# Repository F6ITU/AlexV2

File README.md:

# Alexandrie_V2

Dual ADC OpenHPSDR frontend control board

  **Pour plus d'informations, reportez-vous au Wiki de la page [Alexandrie](https://github.com/F6ITU/Alexandrie)**
  **For more information, please refer to the [Alexandrie](https://github.com/F6ITU/Alexandrie) wiki page**

Kicad files

* Control board for Alexiares filter set driven by an Orion/OrionMK2/Anvelina SDR board with dual 16 bits ADC

This board supports the SPI "Alexiares" protocol (also called "J15") of 
the original Hermes SDR board designed by the OpenHPSDR group.

This second version drives a dual RX BPF filter. 
It also remains compatible with older versions of Alex (see assembly notes

As the third generation of Alexiares frontend is not sold by Apache but still under an open hardware licence, 
a new and more "modular" design was needed by many hams wishing to home-build a "Orion class" fontend

A common Gerber set of files will be used for both RX filters (one with a "RX2_GND" relay, one with a strap on the relay footprint)

TX filter depends on user's choice. The original 150W Alexiares lpf (https://github.com/F6ITU/Alexiares_LPF)
or LA2NI Zolotarev 600W LPF (https://github.com/LA2NI/Zolotarev-LPF)
This board could also be used with the new Aries ATU/Zolotarev lpf/Munin400 high power frontend

This work is protected by the TAPR Open Hardware Licence https://www.tapr.org/ohl.html
Original work by Graham Haddock, KE9H and Phil Harman, VK6APH.

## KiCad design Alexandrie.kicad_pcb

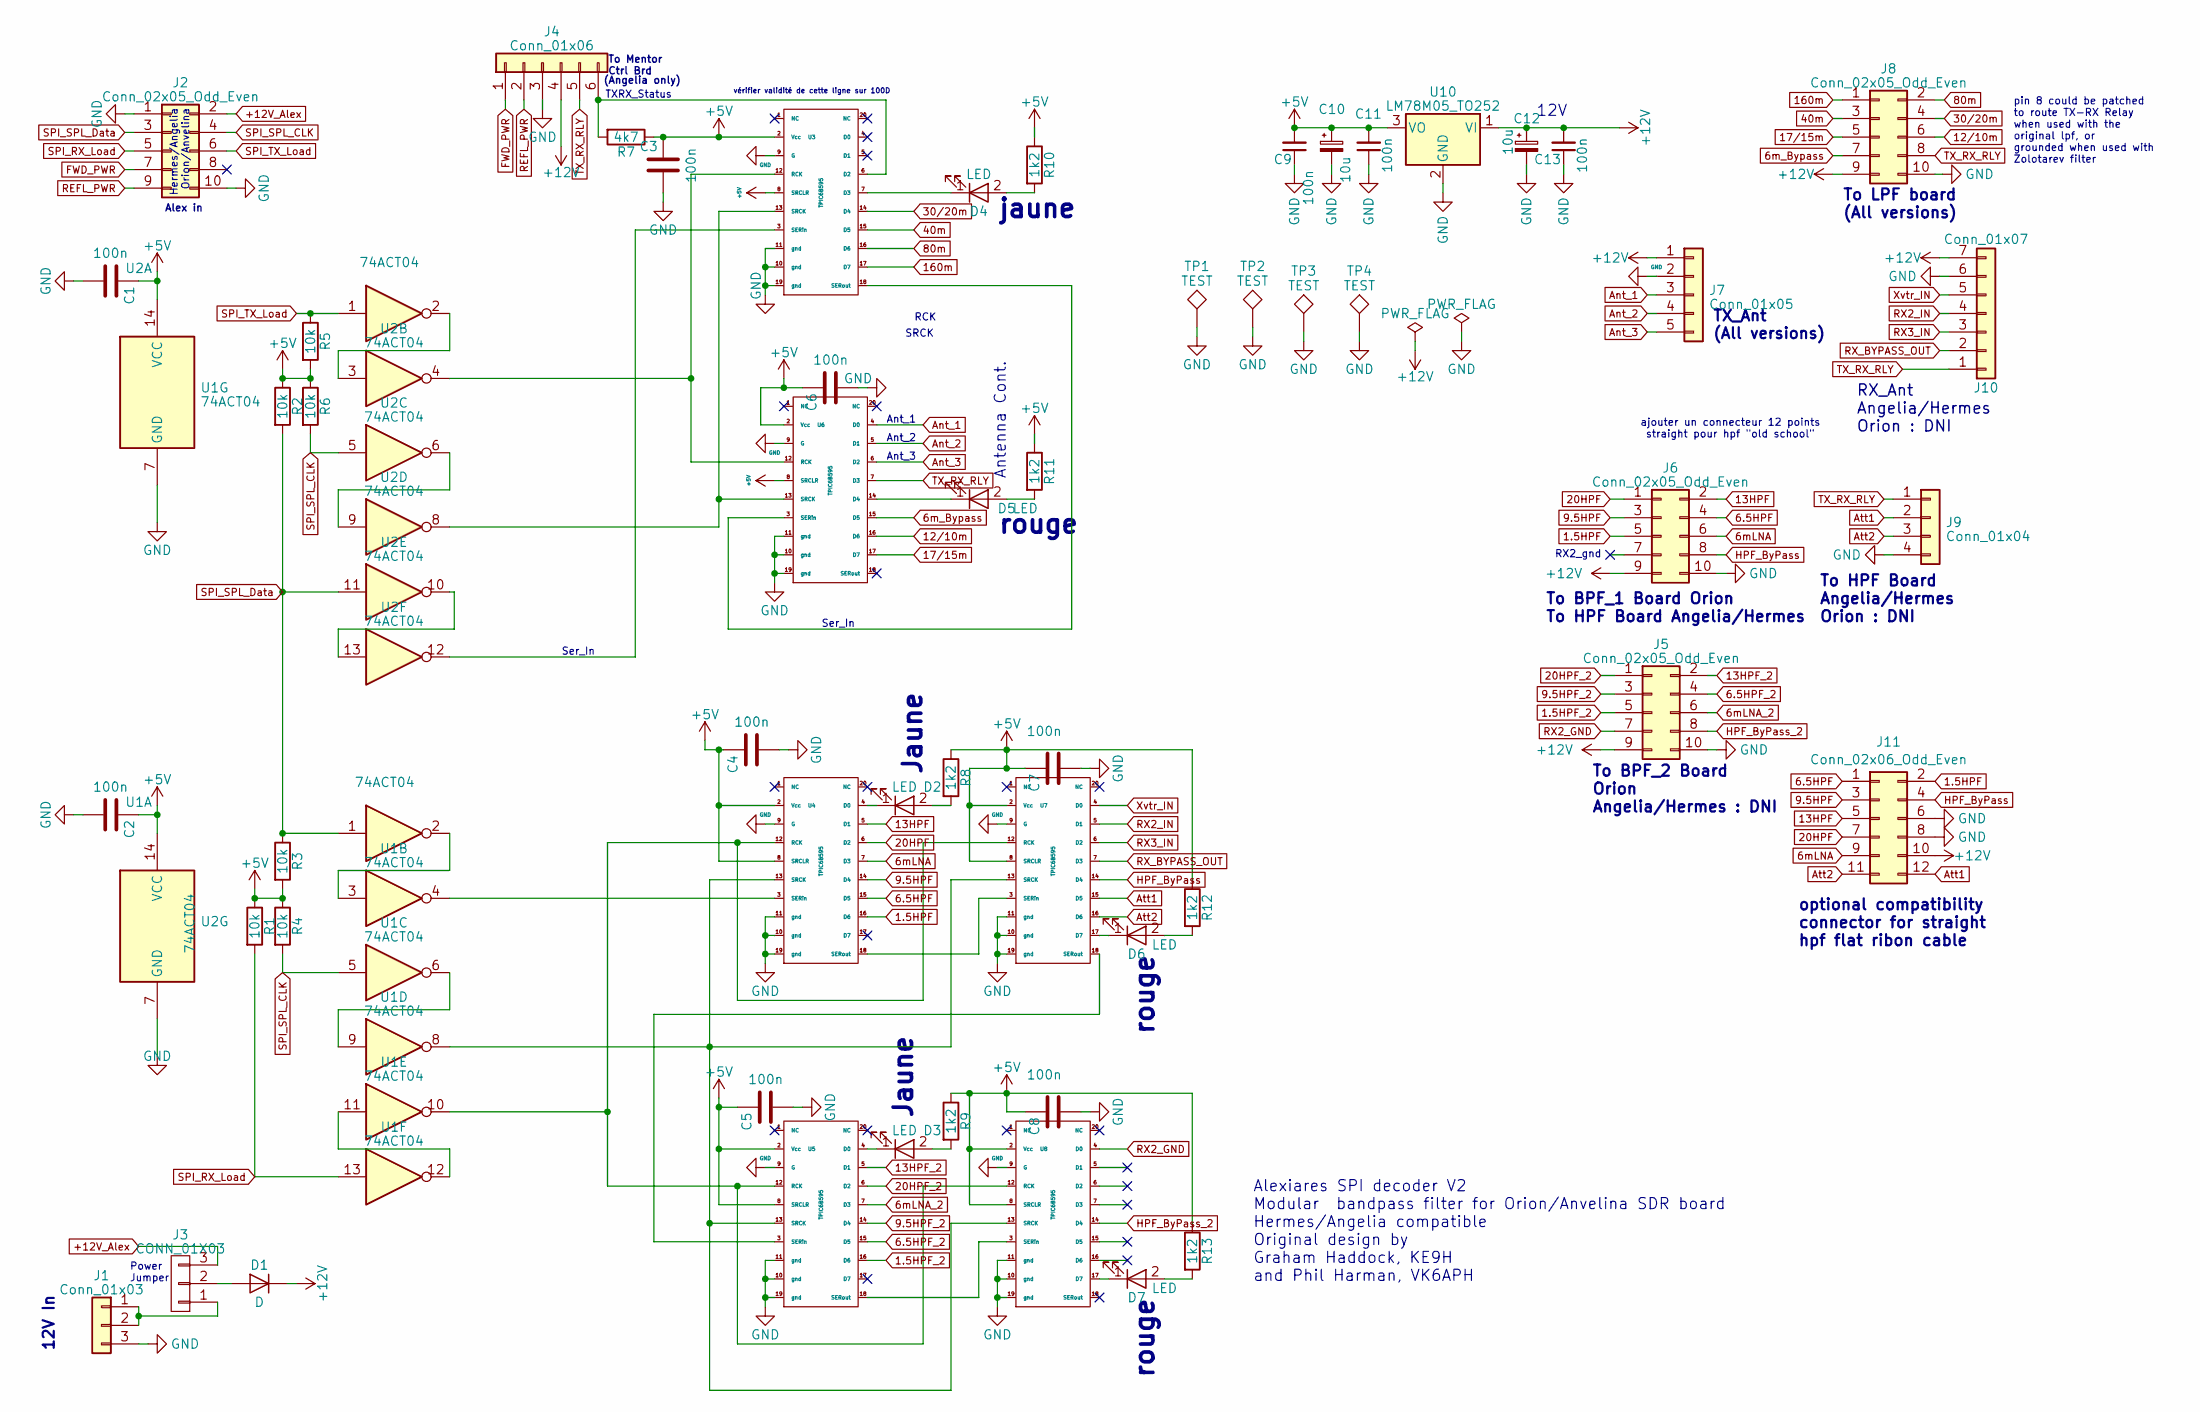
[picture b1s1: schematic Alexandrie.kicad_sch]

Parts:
C1, C2, C3, C4, C5, C6, C7, C8, C9, C11, C13: 100n; C_0805_2012Metric_Pad1.18x1.45mm_HandSolder
C10, C12: 10u; CP_EIA-3528-12_Kemet-T_Pad1.50x2.35mm_HandSolder
D1: D; D_SMB_Handsoldering
D2, D3, D4, D5, D6, D7: LED; LED_1206_3216Metric_Pad1.42x1.75mm_HandSolder
J1: Conn_01x03; Molex_KK-254_AE-6410-03A_1x03_P2.54mm_Vertical
J2, J5, J6, J8: Conn_02x05_Odd_Even; IDC-Header_2x05_P2.54mm_Vertical
J3: CONN_01X03; PinHeader_1x03_P2.54mm_Vertical
J4: Conn_01x06; Molex_KK-254_AE-6410-06A_1x06_P2.54mm_Vertical
J7: Conn_01x05; Molex_KK-254_AE-6410-05A_1x05_P2.54mm_Vertical
J9: Conn_01x04; Molex_KK-254_AE-6410-04A_1x04_P2.54mm_Vertical
J10: Conn_01x07; Molex_KK-254_AE-6410-07A_1x07_P2.54mm_Vertical
J11: Conn_02x06_Odd_Even; IDC-Header_2x06_P2.54mm_Vertical
R1, R2, R3, R4, R5, R6: 10k; R_0805_2012Metric_Pad1.20x1.40mm_HandSolder
R7: 4k7; R_0805_2012Metric_Pad1.20x1.40mm_HandSolder
R8, R9, R10, R11, R12, R13: 1k2; R_0805_2012Metric_Pad1.20x1.40mm_HandSolder
TP1, TP2, TP3, TP4: TEST; MountingHole_3.5mm_Pad_Via
U1, U2: 74ACT04; SOIC-14_3.9x8.7mm_P1.27mm
U3, U4, U5, U6, U7, U8: TPIC6B595; SOIC-20W_7.5x12.8mm_P1.27mm
U10: LM78M05_TO252; TO-252-3_TabPin2

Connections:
1.5HPF: J6.5, J11.2, U4.16 (D6)
1.5HPF_2: J5.5, U5.16 (D6)
6.5HPF: J6.4, J11.1, U4.15 (D5)
6.5HPF_2: J5.4, U5.15 (D5)
6mLNA: J6.6, J11.9, U4.7 (D3)
6mLNA_2: J5.6, U5.7 (D3)
6m_Bypass: J8.7, U6.15 (D5)
9.5HPF: J6.3, J11.3, U4.14 (D4)
9.5HPF_2: J5.3, U5.14 (D4)
12/10m: J8.6, U6.16 (D6)
13HPF: J6.2, J11.5, U4.5 (D1)
13HPF_2: J5.2, U5.5 (D1)
17/15m: J8.5, U6.17 (D7)
20HPF: J6.1, J11.7, U4.6 (D2)
20HPF_2: J5.1, U5.6 (D2)
30/20m: J8.4, U3.14 (D4)
40m: J8.3, U3.15 (D5)
80m: J8.2, U3.16 (D6)
160m: J8.1, U3.17 (D7)
+5V: C1.1, C2.1, C3.1, C4.1, C5.1, C6.1, C7.1, C8.1, C9.2, C10.1, C11.2, R1.1, R2.1, R3.2, R4.1, R5.2, R6.1, R7.1, R8.1, R9.1, R10.1, R11.1, R12.1, R13.1, U1.14 (VCC), U2.14 (VCC), U3.2 (Vcc), U3.8 (SRCLR), U4.2 (Vcc), U4.8 (SRCLR), U5.2 (Vcc), U5.8 (SRCLR), U6.2 (Vcc), U6.8 (SRCLR), U7.2 (Vcc), U7.8 (SRCLR), U8.2 (Vcc), U8.8 (SRCLR), U10.3 (VO)
+12V: C12.1, C13.2, D1.1 (K), J4.4, J5.9, J6.9, J7.1, J8.9, J10.7, J11.10, U10.1 (VI)
+12V_Alex: J2.2, J3.3
Ant_1: J7.3, U6.4 (D0)
Ant_2: J7.4, U6.5 (D1)
Ant_3: J7.5, U6.6 (D2)
Att1: J9.2, J11.12, U7.15 (D5)
Att2: J9.3, J11.11, U7.16 (D6)
FWD_PWR: J2.7, J4.1
GND: C1.2, C2.2, C3.2, C4.2, C5.2, C6.2, C7.2, C8.2, C9.1, C10.2, C11.1, C12.2, C13.1, J1.3, J2.1, J2.10, J4.3, J5.10, J6.10, J7.2, J8.10, J9.4, J10.6, J11.6, J11.8, TP1.1, TP2.1, TP3.1, TP4.1, U1.7 (GND), U2.7 (GND), U3.9 (G), U3.10 (gnd), U3.11 (gnd), U3.19 (gnd), U4.9 (G), U4.10 (gnd), U4.11 (gnd), U4.19 (gnd), U5.9 (G), U5.10 (gnd), U5.11 (gnd), U5.19 (gnd), U6.9 (G), U6.10 (gnd), U6.11 (gnd), U6.19 (gnd), U7.9 (G), U7.10 (gnd), U7.11 (gnd), U7.19 (gnd), U8.9 (G), U8.10 (gnd), U8.11 (gnd), U8.19 (gnd), U10.2 (GND)
HPF_ByPass: J6.8, J11.4, U7.14 (D4)
HPF_ByPass_2: J5.8, U8.14 (D4)
unnamed: D1.2 (A), J3.2
unnamed: D2.2 (A), R8.2
unnamed: D2.1 (K), U4.4 (D0)
unnamed: D3.2 (A), R9.2
unnamed: D3.1 (K), U5.4 (D0)
unnamed: D4.2 (A), R10.2
unnamed: D4.1 (K), U3.7 (D3)
unnamed: D5.2 (A), R11.2
unnamed: D5.1 (K), U6.14 (D4)
unnamed: D6.2 (A), R12.2
unnamed: D6.1 (K), U7.17 (D7)
unnamed: D7.2 (A), R13.2
unnamed: D7.1 (K), U8.17 (D7)
unnamed: J1.1, J1.2, J3.1
unnamed: J4.6, R7.2, U3.6 (D2)
unnamed: U1.2, U1.3
unnamed: U1.6, U1.9
unnamed: U1.11, U1.12
unnamed: U2.2, U2.3
unnamed: U2.6, U2.9
unnamed: U2.10, U2.13
unnamed: U2.4, U3.12 (RCK), U6.12 (RCK)
unnamed: U2.12, U3.3 (SERin)
unnamed: U3.18 (SERout), U6.3 (SERin)
unnamed: U2.8, U3.13 (SRCK), U6.13 (SRCK)
unnamed: U1.10, U4.12 (RCK), U5.12 (RCK), U7.12 (RCK), U8.12 (RCK)
unnamed: U1.4, U4.3 (SERin)
unnamed: U4.18 (SERout), U7.3 (SERin)
unnamed: U1.8, U4.13 (SRCK), U5.13 (SRCK), U7.13 (SRCK), U8.13 (SRCK)
unnamed: U5.3 (SERin), U7.18 (SERout)
unnamed: U5.18 (SERout), U8.3 (SERin)
REFL_PWR: J2.9, J4.2
RX2_GND: J5.7, U8.4 (D0)
RX2_IN: J10.4, U7.5 (D1)
RX3_IN: J10.3, U7.6 (D2)
RX_BYPASS_OUT: J10.2, U7.7 (D3)
SPI_RX_Load: J2.5, R1.2, U1.13
SPI_SPL_CLK: J2.4, R4.2, R6.2, U1.5, U2.5
SPI_SPL_Data: J2.3, R2.2, R3.1, U1.1, U2.11
SPI_TX_Load: J2.6, R5.1, U2.1
TX_RX_RLY: J4.5, J8.8, J9.1, J10.1, U6.7 (D3)
Xvtr_IN: J10.5, U7.4 (D0)

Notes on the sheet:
SRCK
To HPF Board Angelia/Hermes Orion : DNI
(Angelia only)
Jaune
Ant_1
Antenna Cont.
To BPF_2 Board Orion Angelia/Hermes : DNI
Ant_3
Power Jumper
jaune
rouge
TXRX_Status
optional compatibility connector for straight hpf flat ribon cable
ajouter un connecteur 12 points straight pour hpf "old school"
RCK
Ser_In
To BPF_1 Board Orion To HPF Board Angelia/Hermes
RX_Ant Angelia/Hermes Orion : DNI
Alexiares SPI decoder V2 Modular bandpass filter for Orion/Anvelina SDR board Hermes/Angelia compatible Original design by Graham Haddock, KE9H and Phil Harman, VK6APH
RX2_gnd
12V
TX_Ant (All versions)
12V In
Alex in
Hermes/Angelia Orion/Anvelina
pin 8 could be patched to route TX-RX Relay when used with the original lpf, or grounded when used with Zolotarev filter
vérifier validité de cette ligne sur 100D
To Mentor Ctrl Brd
Ant_2
To LPF board (All versions)
rouge

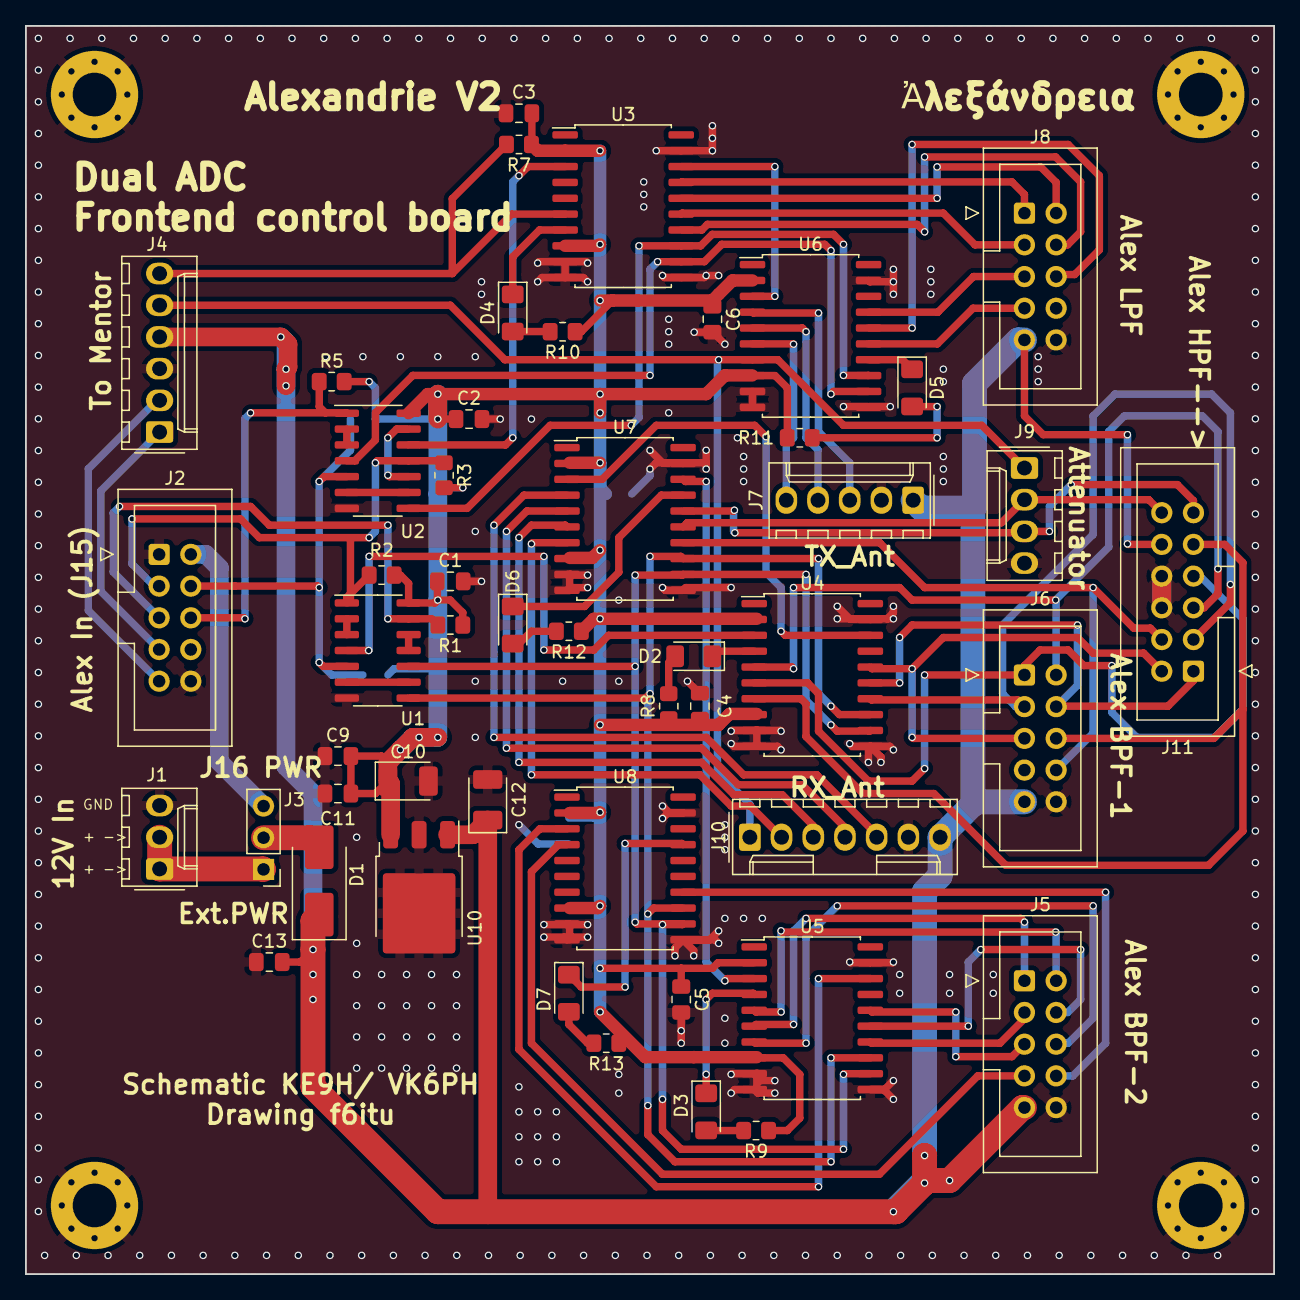
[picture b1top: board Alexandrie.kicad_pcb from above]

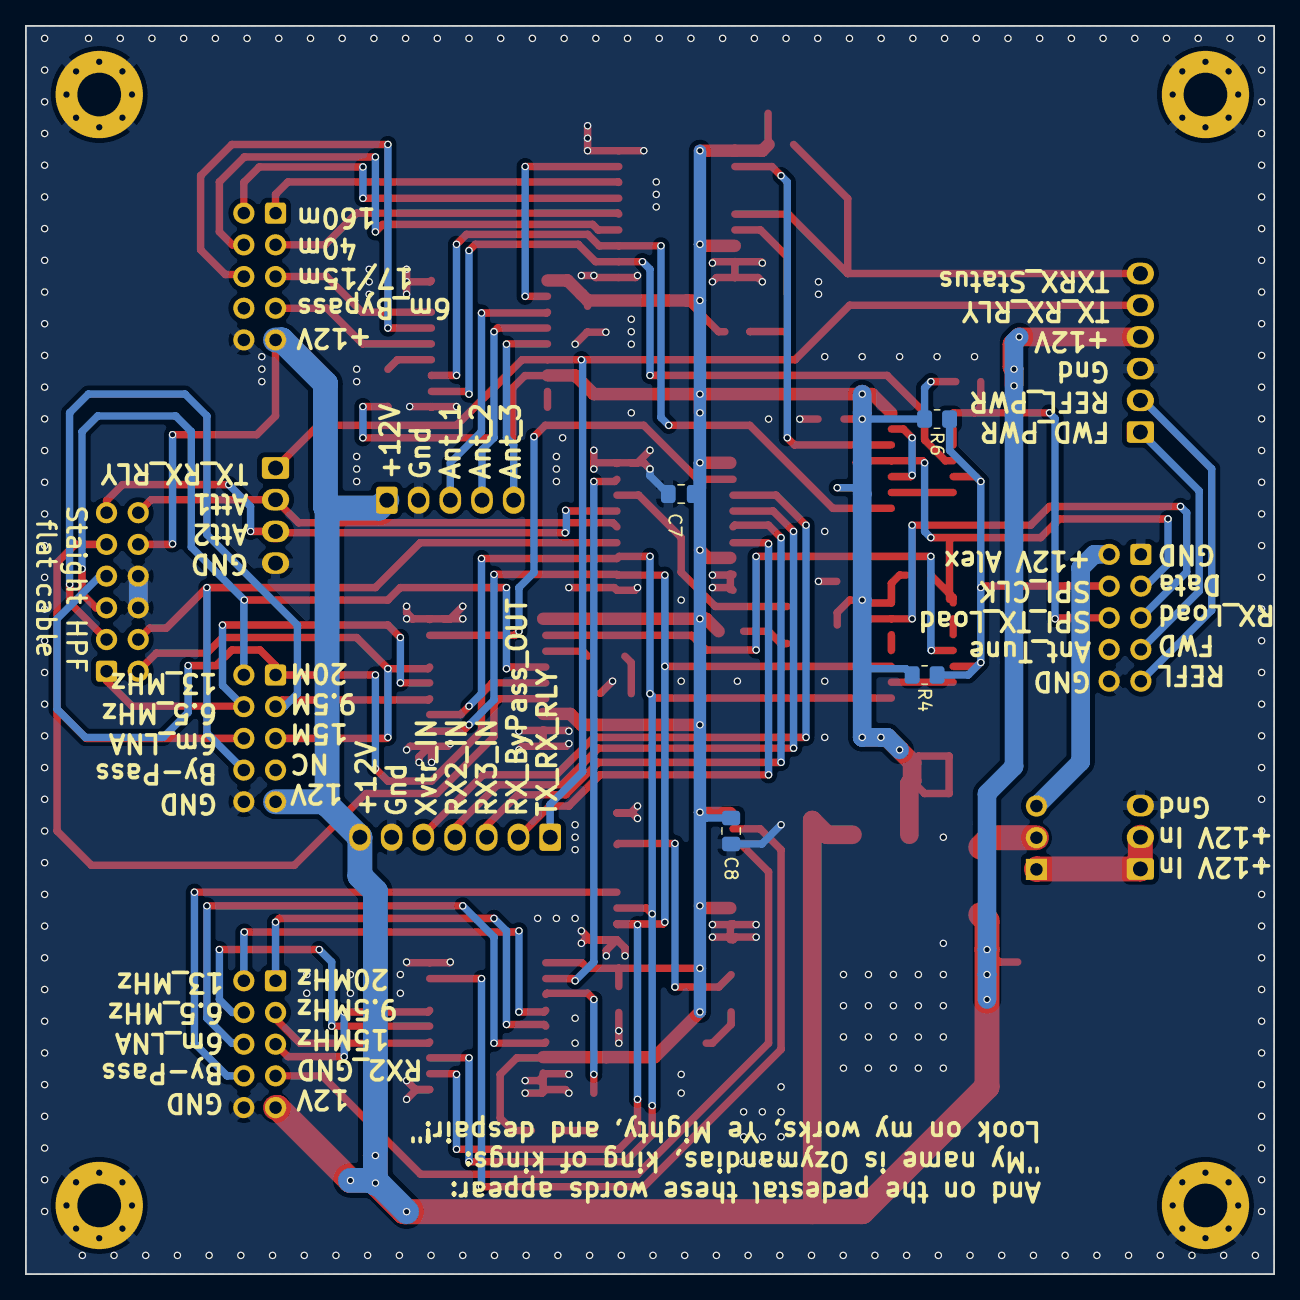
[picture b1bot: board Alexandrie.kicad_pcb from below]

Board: 2 copper layers, 100.0 x 100.0 mm, 57 parts (4 on the bottom side), 73 nets.

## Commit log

2023-04-12 initial design
2023-04-13 first RTM with silkmask
2023-04-13 DRC clean, iBom saved
2023-04-13 new readme
2023-04-17 new readme, new ibom, new schematic pdf
2023-04-18 schematic pdf added
2023-05-18 minor chages, new iBom
2023-05-18 minor chages, new iBom, new readme, new picture
2026-05-17 kicad 10 update, new readme, new wiki link
